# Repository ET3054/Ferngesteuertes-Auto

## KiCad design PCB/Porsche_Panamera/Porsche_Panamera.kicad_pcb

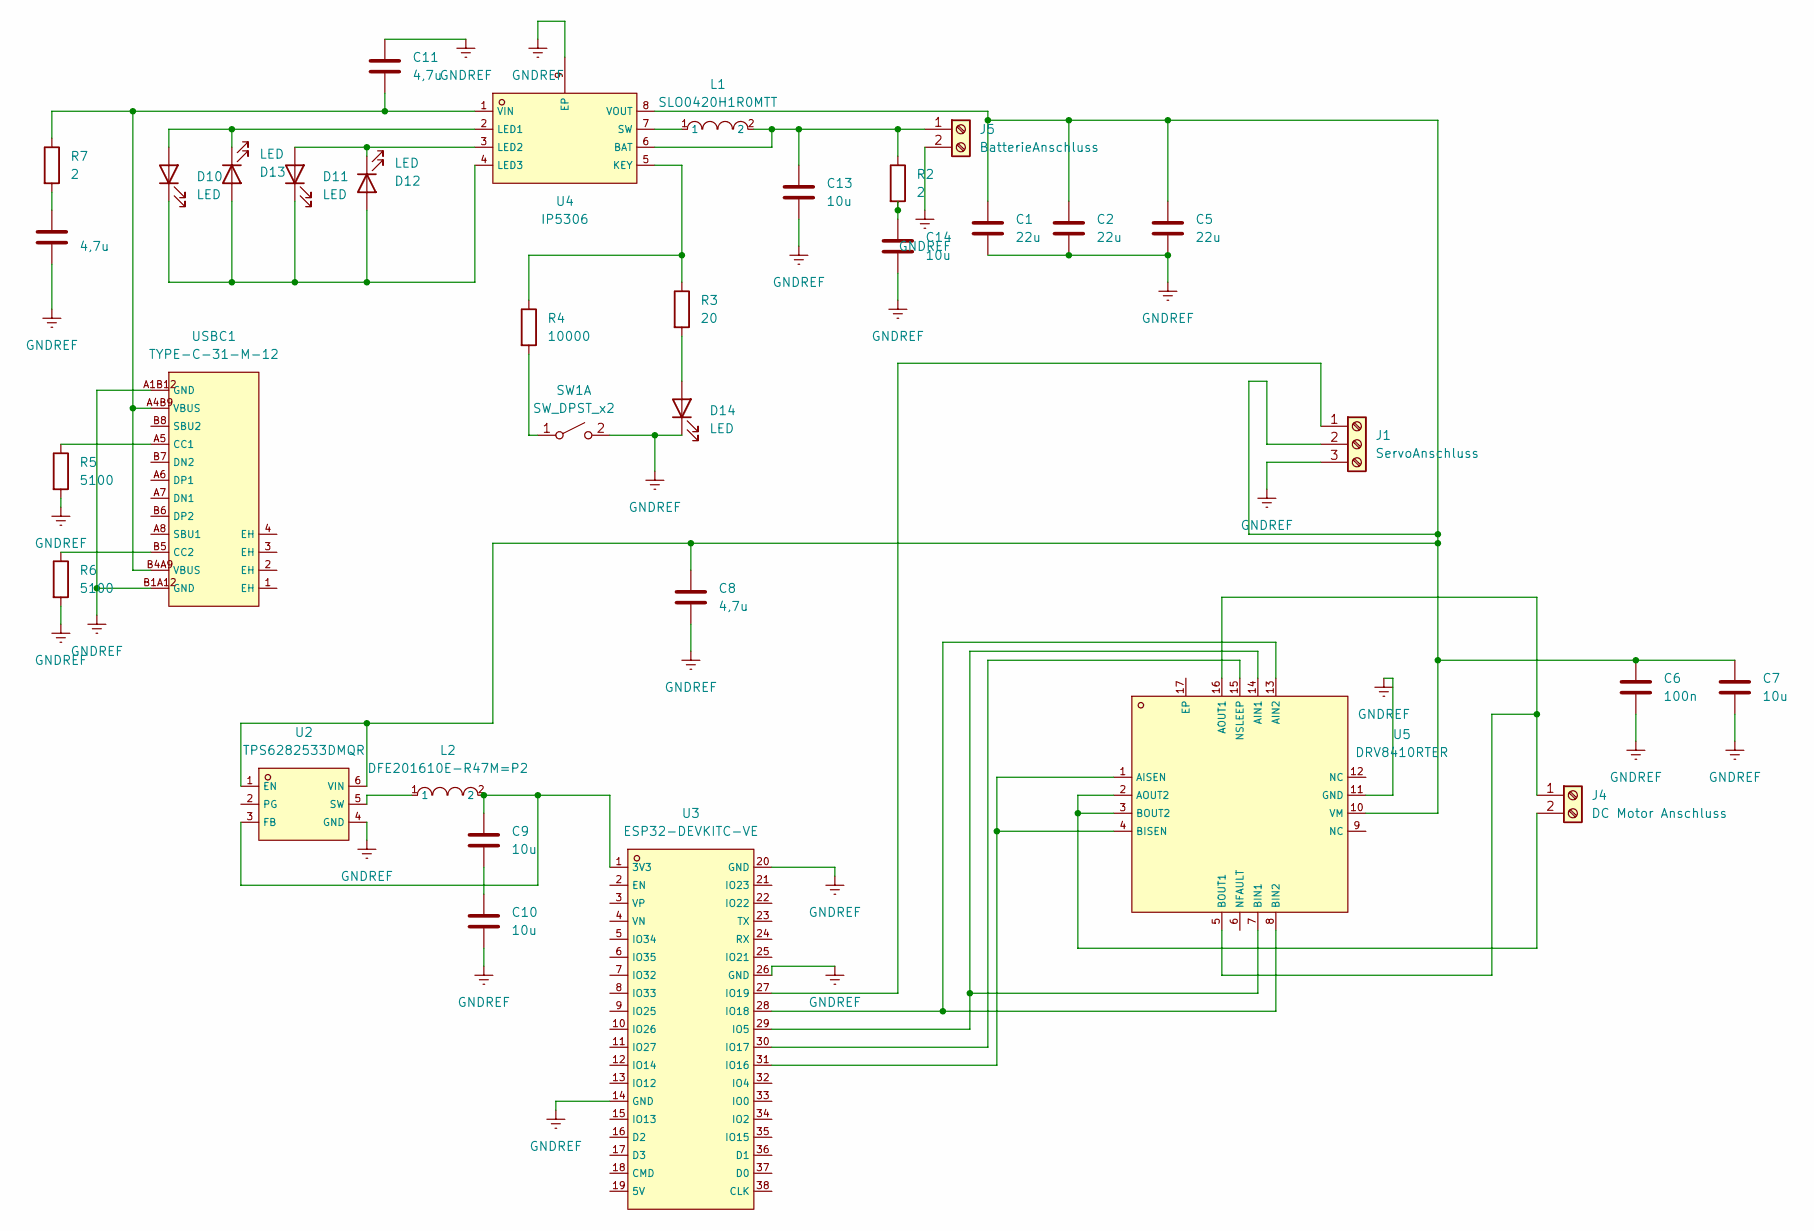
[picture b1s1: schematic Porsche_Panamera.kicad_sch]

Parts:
C1, C2, C5: 22u; C_0805_2012Metric
C6: 100n; C_0805_2012Metric
C7, C9, C10, C13, C14: 10u; C_0805_2012Metric
C8, C11, C12: 4,7u; C_0805_2012Metric
D10, D11, D12, D13, D14: LED; LED_D5.0mm
J1: ServoAnschluss; TerminalBlock_Phoenix_MKDS-1,5-3-5.08_1x03_P5.08mm_Horizont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
J4: DC Motor Anschluss; TerminalBlock_Phoenix_MKDS-1,5-2-5.08_1x02_P5.08mm_Horizont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
J5: BatterieAnschluss; TerminalBlock_Phoenix_MKDS-1,5-2-5.08_1x02_P5.08mm_Horizont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
L1: SLO0420H1R0MTT; C207826_IND-SMD_L4_4-W4_2; LCSC C207826
L2: DFE201610E-R47M=P2; C269773_L0806; LCSC C269773
R2, R7: 2; R_0805_2012Metric
R3: 20; R_0805_2012Metric
R4: 10000; R_0805_2012Metric
R5, R6: 5100; R_0805_2012Metric
SW1: SW_DPST_x2; SW_PUSH_6mm
U2: TPS6282533DMQR; C3189971_VSON-6_L1_5-W1_5-P0_50-TL; LCSC C3189971
U3: ESP32-DEVKITC-VE; C20437001_BULETM-SMD_ESP32-DEVKITC; LCSC C20437001
U4: IP5306; C181692_ESOP-8_L4_9-W3_9-P1_27-LS6_0-BL-EP; LCSC C181692
U5: DRV8410RTER; C6183906_WQFN-16_L3_0-W3_0-P0_50-BL-EP1_7; LCSC C6183906
USBC1: TYPE-C-31-M-12; C165948_USB-C_SMD-TYPE-C-31-M-12_1; LCSC C165948

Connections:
GNDREF: C1.2, C2.2, C5.2, C6.2, C7.2, C8.2, C10.2, C11.1, C12.2, C13.2, C14.2, D14.1 (K), J1.3, J5.2, R5.2, R6.2, SW1.2 (B), U2.4 (GND), U3.14 (GND), U3.20 (GND), U3.26 (GND), U4.9 (EP), U5.11 (GND), USBC1.A1B12 (GND), USBC1.B1A12 (GND)
unnamed: C9.2, C10.1
unnamed: C12.1, R7.2
unnamed: C14.1, R2.2
unnamed: D10.2 (A), D13.1 (K), U4.2 (LED1)
unnamed: D10.1 (K), D11.1 (K), D12.2 (A), D13.2 (A), U4.4 (LED3)
unnamed: D11.2 (A), D12.1 (K), U4.3 (LED2)
unnamed: D14.2 (A), R3.2
unnamed: J1.1, U3.27 (IO19)
unnamed 9: C1.1, C2.1, C5.1, C6.1, C7.1, C8.1, J1.2, U2.1 (EN), U2.6 (VIN), U4.8 (VOUT), U5.10 (VM); also elsewhere on the board
unnamed: J4.1, U5.5 (BOUT1), U5.16 (AOUT1)
unnamed: J4.2, U5.2 (AOUT2), U5.3 (BOUT2)
unnamed: C13.1, J5.1, L1.2, R2.1, U4.6 (BAT)
unnamed: R4.2, SW1.1 (A)
unnamed 14: C9.1, L2.2, U2.3 (FB), U3.1 (3V3); also elsewhere on the board
unnamed: L2.1, U2.5 (SW)
unnamed: U3.29 (IO5), U5.7 (BIN1), U5.14 (AIN1)
unnamed: U3.31 (IO16), U5.1 (AISEN), U5.4 (BISEN)
unnamed: U3.30 (IO17), U5.15 (NSLEEP)
unnamed: U3.28 (IO18), U5.8 (BIN2), U5.13 (AIN2)
unnamed: R3.1, R4.1, U4.5 (KEY)
unnamed: L1.1, U4.7 (SW)
unnamed: C11.2, R7.1, U4.1 (VIN), USBC1.A4B9 (VBUS), USBC1.B4A9 (VBUS)
unnamed: R5.1, USBC1.A5 (CC1)
unnamed: R6.1, USBC1.B5 (CC2)

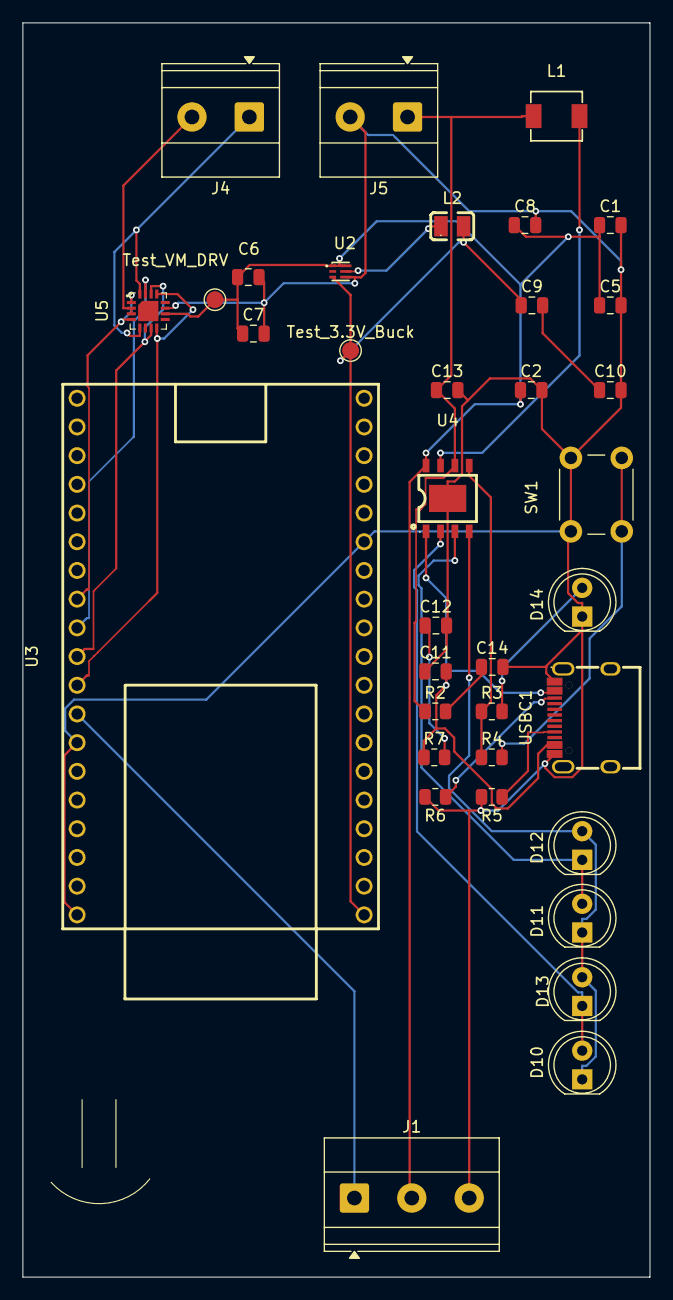
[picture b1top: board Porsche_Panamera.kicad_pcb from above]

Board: 2 copper layers, 55.5 x 111.0 mm, 36 parts (0 on the bottom side), 25 nets.

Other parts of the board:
Test_3.3V_Buck: TestPoint_Pad_D1.5mm
Test_VM_DRV: TestPoint_Pad_D1.5mm

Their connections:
unnamed 9: Test_VM_DRV.1; also elsewhere on the board
unnamed 14: Test_3.3V_Buck.1; also elsewhere on the board

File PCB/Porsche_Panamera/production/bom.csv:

Designator,Footprint,Quantity,Value,LCSC Part #
"C1, C2, C5",0805,3,22u,
"C10, C13, C14, C7, C9",0805,5,10u,
"C11, C12, C8",0805,3,"4,7u",
C6,0805,1,100n,
"D10, D11, D12, D13, D14",LED_D5.0mm,5,LED,
J1,"TerminalBlock_Phoenix_MKDS-1,5-3-5.08_1x03_P5.08mm_Horizontal",1,ServoAnschluss,
J4,"TerminalBlock_Phoenix_MKDS-1,5-2-5.08_1x02_P5.08mm_Horizontal",1,DC Motor Anschluss,
J5,"TerminalBlock_Phoenix_MKDS-1,5-2-5.08_1x02_P5.08mm_Horizontal",1,BatterieAnschluss,
L1,C207826_IND-SMD_L4_4-W4_2,1,SLO0420H1R0MTT,C207826
L2,C269773_L0806,1,DFE201610E-R47M=P2,C269773
"R2, R7",0805,2,2,
R3,0805,1,20,
R4,0805,1,10000,
"R5, R6",0805,2,5100,
SW1,SW_PUSH_6mm,1,SW_DPST_x2,
U2,C3189971_VSON-6_L1_5-W1_5-P0_50-TL,1,TPS6282533DMQR,C3189971
U3,C20437001_BULETM-SMD_ESP32-DEVKITC,1,ESP32-DEVKITC-VE,C20437001
U4,C181692_ESOP-8_L4_9-W3_9-P1_27-LS6_0-BL-EP,1,IP5306,C181692
U5,C6183906_WQFN-16_L3_0-W3_0-P0_50-BL-EP1_7,1,DRV8410RTER,C6183906
USBC1,C165948_USB-C_SMD-TYPE-C-31-M-12_1,1,TYPE-C-31-M-12,C165948
